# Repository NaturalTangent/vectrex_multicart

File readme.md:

# Vectrex Multicart

This is a PCB for a simple vectrex multicart. Games are selected using DIP switches on the cart (power-off first).

The PCB was developed using kicad (not sure which version, it was a few years ago...). I've just re-discovered it on my hard disk and converted to kicad 6.0.0.

## Schematic

I think the original schematic came from https://harmlesslion.com/text/vectrex_multicart.htm

## PCB

## Cart EPROM

_make8k_ is a quick and dirty tool for concatenating multiple game ROMs into a single binary that can be written to the cart.

The resulting binary must be written to the EPROM using an EPROM burner (e.g. TL866).

### make8k

To build you will need a C++ compiler. On linux it can be built as follows;

```shell
gcc ./make8k.cpp -o make8k
```

Using it to generate the EPROM binary requires a set of vectrex ROMs (you'll need to find these elsewhere) and a simple configuration file.

The configuration file is a list of the ROM file names, one per line for each of the ROMs to be added to the EPROM. E.g.

```
ARMOR.bin
BEDLAM.bin
BERZERK.bin
BLITZ.bin
CASTLE.bin
CHASM.bin
CRAZY.bin
DUALVEC2.bin
HEADSUP.bin
HYPER.bin
LANDER.bin
MELODY.bin
MINE3.bin
NARROW.bin
NARZOD.bin
PATRIOT.bin
POLAR.bin
POLE.bin
RIPOFF.bin
SCRAMBLE.bin
SOLAR.bin
SPACE.bin
SPIKE.bin
SPINBALL.bin
STARHAWK.bin
STARTREK.bin
SWEEP.bin
WEBWARS.bin
```

Copy the ROM files, the config file, and the make8k executable into the same folder and then generate the EPROM binary by executing the following;

```shell
make8k config.txt eprom.bin
```

This will generate a file named _eprom.bin_ that can now be written to your EPROM (using an EPROM burner such as a TL866).

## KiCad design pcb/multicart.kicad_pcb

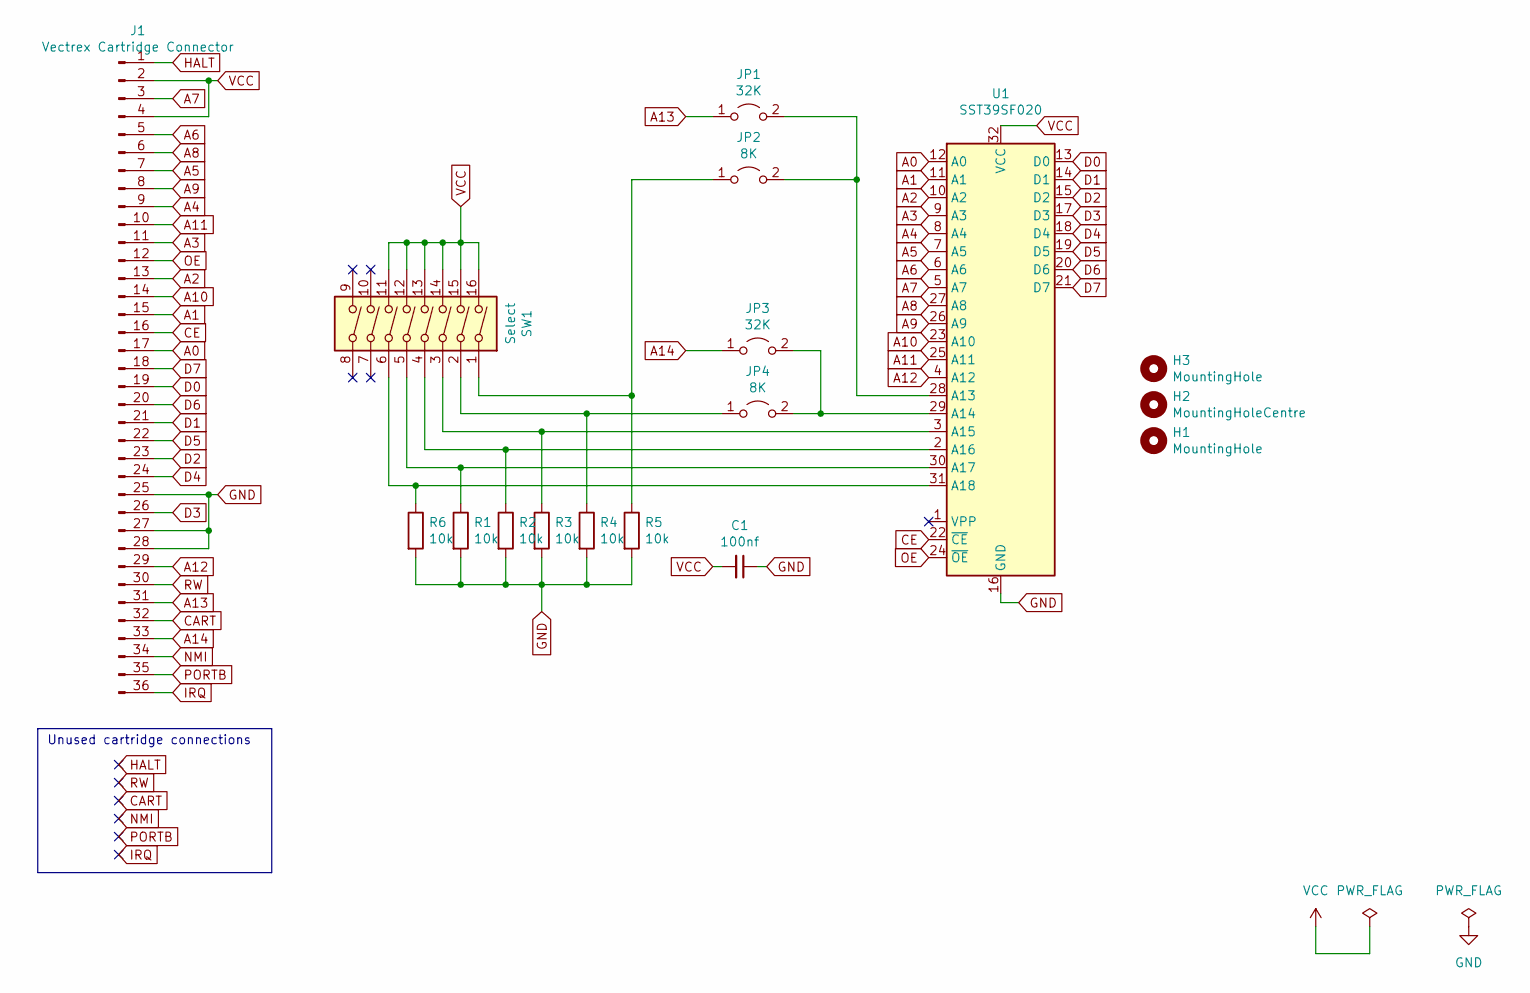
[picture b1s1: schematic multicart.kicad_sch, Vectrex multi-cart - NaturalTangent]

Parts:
C1: 100nf; C_Disc_D4.7mm_W2.5mm_P5.00mm
H1, H3: MountingHole; MountingHole_3.7mm
H2: MountingHoleCentre; MountingHole_5.3mm_M5
J1: Vectrex Cartridge Connector; VECTREX_CART
JP1, JP3: 32K; PinHeader_1x02_P2.54mm_Vertical
JP2, JP4: 8K; PinHeader_1x02_P2.54mm_Vertical
R1, R2, R3, R4, R5, R6: 10k; R_Axial_DIN0207_L6.3mm_D2.5mm_P7.62mm_Horizontal
SW1: Select; SW_DIP_SPSTx08_Slide_9.78x22.5mm_W7.62mm_P2.54mm
U1: SST39SF020; DIP-32_W15.24mm_Socket_LongPads

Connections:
A0: J1.17, U1.12 (A0)
A1: J1.15, U1.11 (A1)
A2: J1.13, U1.10 (A2)
A3: J1.11, U1.9 (A3)
A4: J1.9, U1.8 (A4)
A5: J1.7, U1.7 (A5)
A6: J1.5, U1.6 (A6)
A7: J1.3, U1.5 (A7)
A8: J1.6, U1.27 (A8)
A9: J1.8, U1.26 (A9)
A10: J1.14, U1.23 (A10)
A11: J1.10, U1.25 (A11)
A12: J1.29, U1.4 (A12)
A13: J1.31, JP1.1 (A)
A14: J1.33, JP3.1 (A)
CART: J1.32
CE: J1.16, U1.22 (~CE)
D0: J1.19, U1.13 (D0)
D1: J1.21, U1.14 (D1)
D2: J1.23, U1.15 (D2)
D3: J1.26, U1.17 (D3)
D4: J1.24, U1.18 (D4)
D5: J1.22, U1.19 (D5)
D6: J1.20, U1.20 (D6)
D7: J1.18, U1.21 (D7)
GND: C1.1, J1.25, J1.27, J1.28, R1.2, R2.2, R3.2, R4.2, R5.2, R6.2, U1.16 (GND)
HALT: J1.1
IRQ: J1.36
NMI: J1.34
unnamed: JP1.2 (B), JP2.2 (B), U1.28 (A13)
unnamed: JP2.1 (A), R5.1, SW1.1
unnamed: JP3.2 (B), JP4.2 (B), U1.29 (A14)
unnamed: JP4.1 (A), R4.1, SW1.2
unnamed: R1.1, SW1.5, U1.30 (A17)
unnamed: R2.1, SW1.4, U1.2 (A16)
unnamed: R3.1, SW1.3, U1.3 (A15)
unnamed: R6.1, SW1.6, U1.31 (A18)
OE: J1.12, U1.24 (~OE)
PORTB: J1.35
RW: J1.30
VCC: C1.2, J1.2, J1.4, SW1.11, SW1.12, SW1.13, SW1.14, SW1.15, SW1.16, U1.32 (VCC)

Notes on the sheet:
Unused cartridge connections

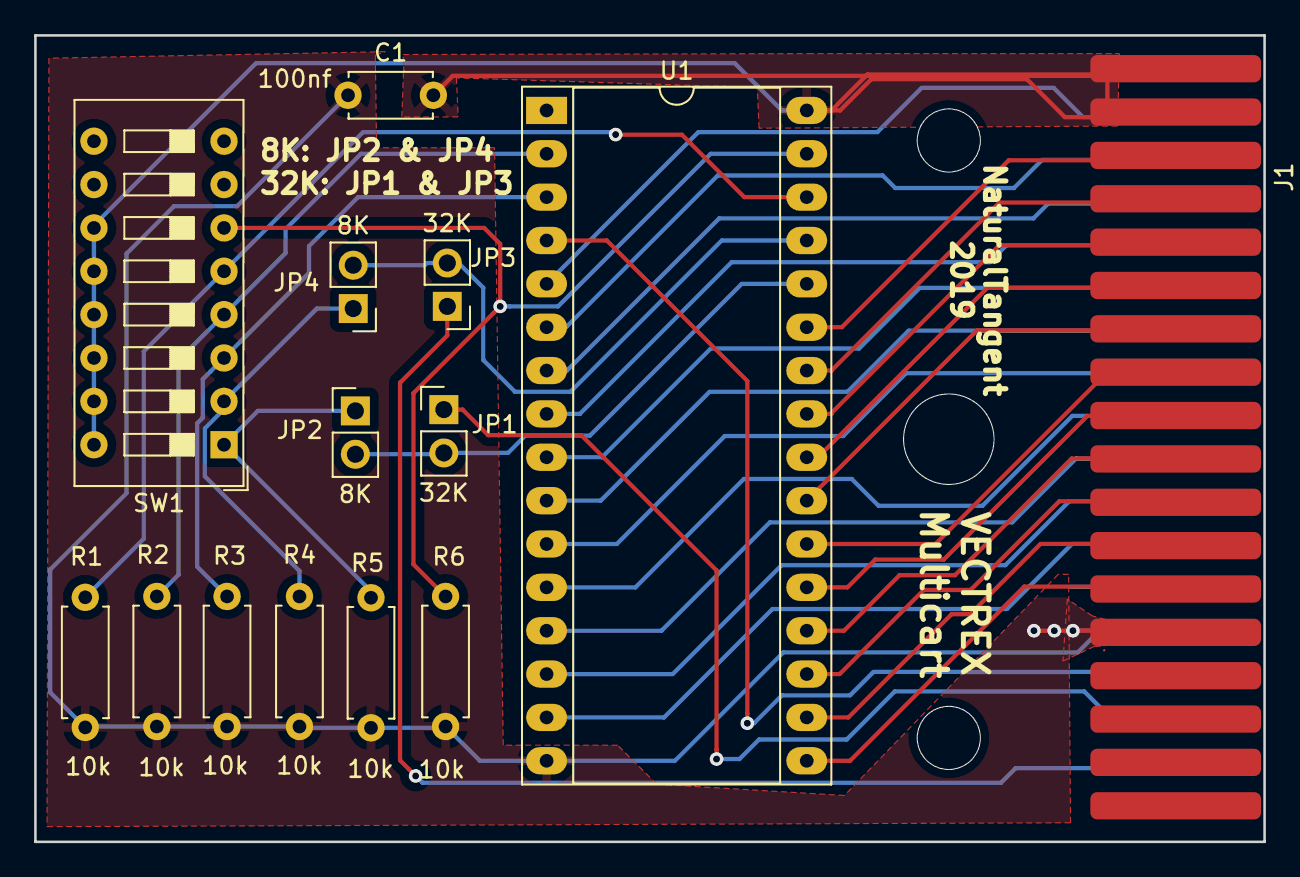
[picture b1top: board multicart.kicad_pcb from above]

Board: 2 copper layers, 72.0 x 47.2 mm, 17 parts (0 on the bottom side), 35 nets.

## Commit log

2021-12-31 A simple Vectrex multicart PCB with a quick and dirty tool for combining game ROMs into a single file for burning to the cartridge.
2021-12-31 Add readme.
2021-12-31 Update image paths in readme.
